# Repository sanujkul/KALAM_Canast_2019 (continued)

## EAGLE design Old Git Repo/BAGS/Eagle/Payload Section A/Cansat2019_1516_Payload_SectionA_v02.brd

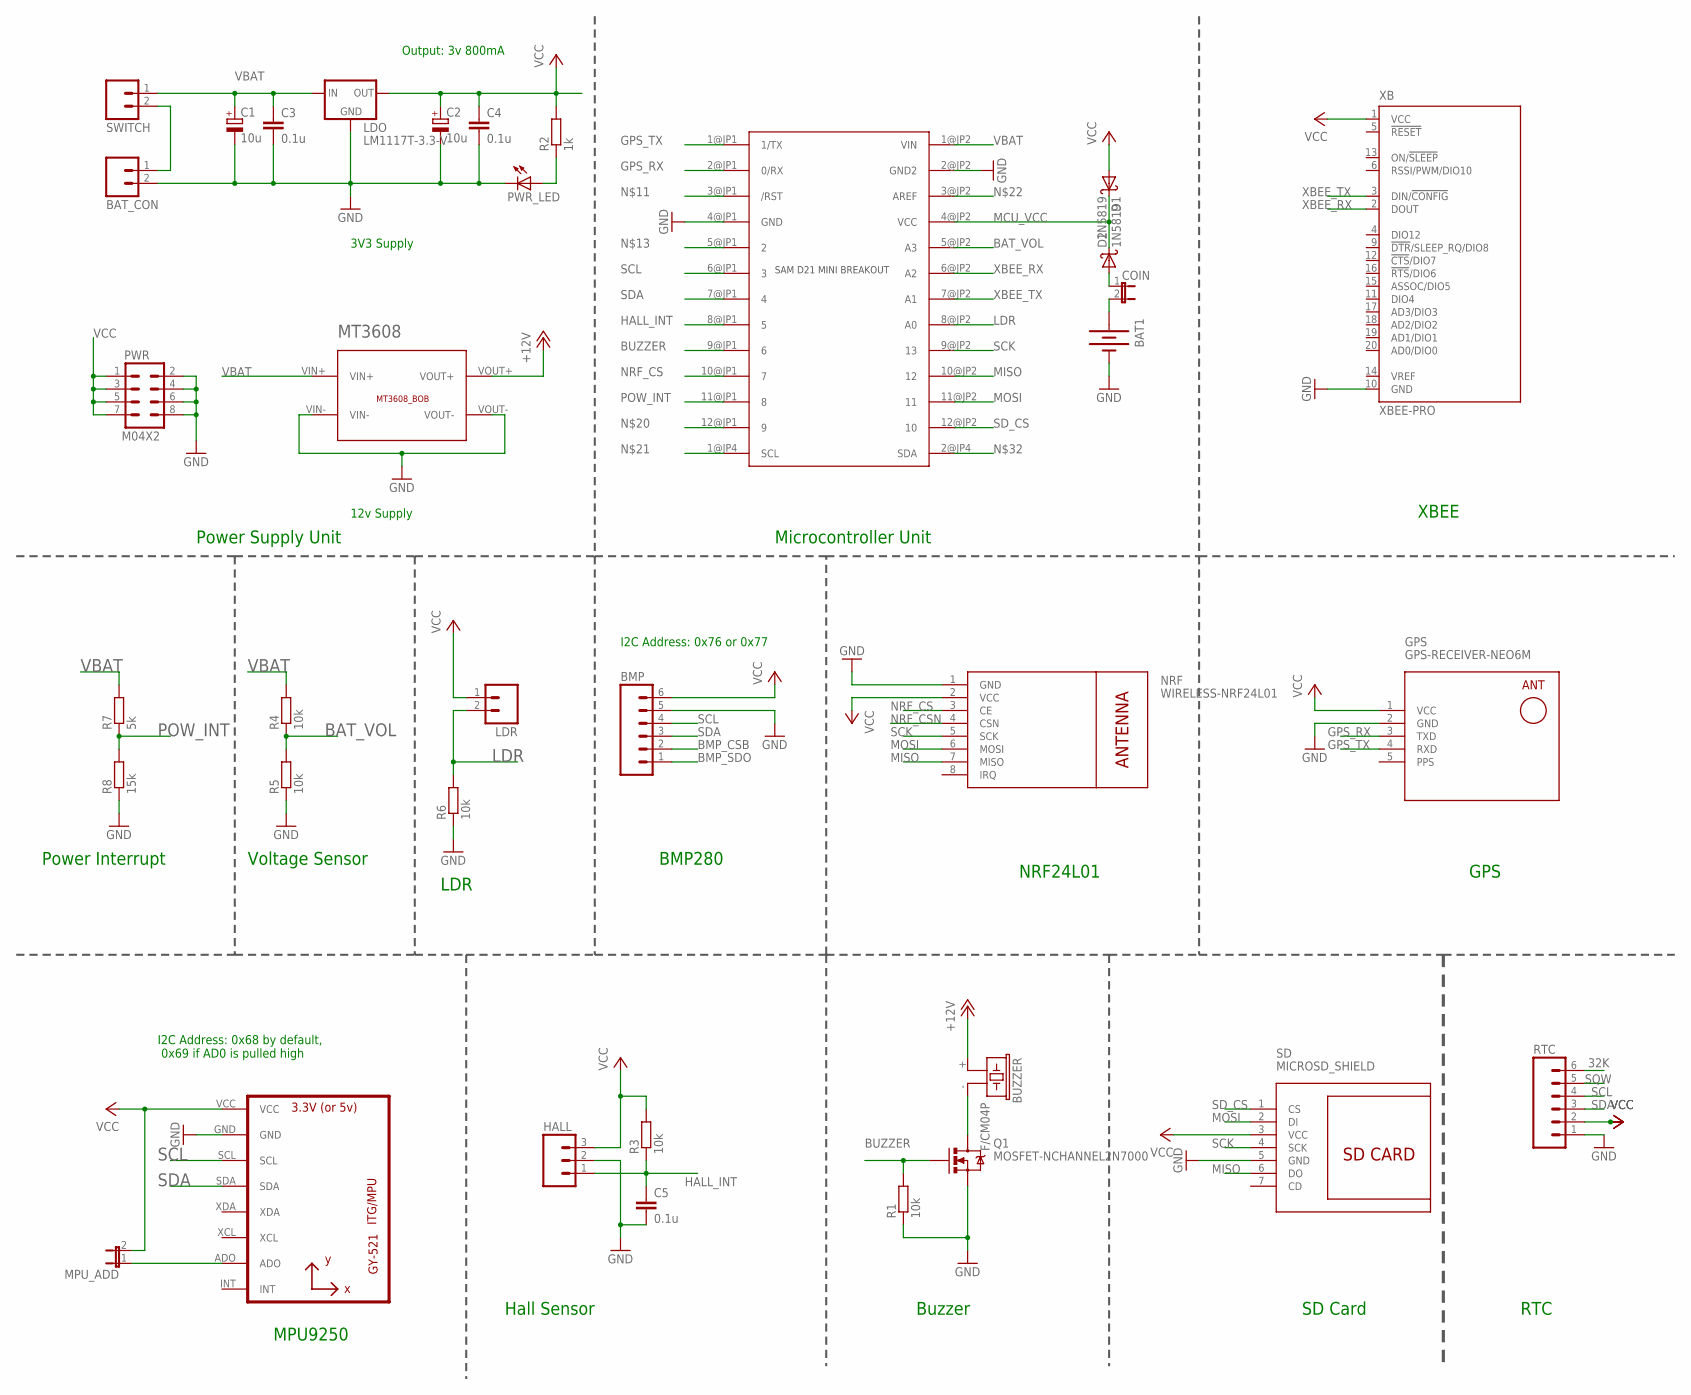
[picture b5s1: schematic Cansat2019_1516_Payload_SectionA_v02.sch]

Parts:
BAT1: BATTERY20PTH; BATTCOM_20MM_PTH
BAT_CON: M02; 02P
BMP: M06; 06P
BUZZER: F/CM04P
C1, C2: 10u; E2,5-6
C3, C4, C5: 0.1u; C025-025X050
COIN: JUMPER-2PTH; 1X02
D1, D2: 1N5819; DO41-10
GPS: GPS-RECEIVER-NEO6M
HALL: M03; 03P
LDO: LM1117T-3.3-V; TO220V
LDR: M02; 02P
MPU: GY-521MPU6050; GY-521
MPU_ADD: JUMPER-2PTH; 1X02
MT3608: MT3608_BOB
NRF: WIRELESS-NRF24L01
PWR: M04X2; 2X4
PWR_LED: LED3MM
Q1: MOSFET-NCHANNEL2N7000; TO-92
R1, R3, R4, R5, R6: 10k; 0204/7
R2: 1k; 0204/7
R7: 5k; 0204/7
R8: 15k; 0204/7
RTC: M06; 06P
SAMD: SAM_D21_MINI_BREAKOUT; JP1_SPARKFUN-SAMD21-MINI-BREAKOUT-V10
SD: MICROSD_SHIELD
SWITCH: M02; 02P
XB: XBEE-PRO

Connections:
32K: RTC.6
+12V: BUZZER.+ (1), MT3608.VOUT+
BAT_VOL: R4.1, R5.2, SAMD.5@JP2 (A3)
BMP_CSB: BMP.2
BMP_SDO: BMP.1
BUZZER: Q1.2 (G), R1.2, SAMD.9@JP1 (6)
GND: BAT1.2 (-), BAT_CON.2, BMP.5, C1.-, C2.-, C3.2, C4.2, C5.2, GPS.2 (GND), HALL.2, LDO.1 (GND), MPU.GND, MT3608.VIN-, MT3608.VOUT-, NRF.1 (GND), PWR.2, PWR.4, PWR.6, PWR.8, PWR_LED.K (C), Q1.1 (S), R1.1, R5.1, R6.1, R8.1, RTC.1, SAMD.2@JP2 (GND2), SAMD.4@JP1 (GND), SD.5 (GND), XB.10 (GND)
GPS_RX: GPS.3 (TXD), SAMD.2@JP1 (0/RX)
GPS_TX: GPS.4 (RXD), SAMD.1@JP1 (1/TX)
HALL_INT: C5.1, HALL.1, R3.1, SAMD.8@JP1 (5)
LDR: LDR.2, R6.2, SAMD.8@JP2 (A0)
MCU_VCC: D1.C, D2.C, SAMD.4@JP2 (VCC)
MISO: NRF.7 (MISO), SAMD.10@JP2 (12), SD.6 (DO)
MOSI: NRF.6 (MOSI), SAMD.11@JP2 (11), SD.2 (DI)
unnamed: BUZZER.- (2), Q1.3 (D)
unnamed: COIN.1, D2.A
unnamed: PWR_LED.A, R2.1
unnamed: BAT1.1 (+), COIN.2
unnamed: BAT_CON.1, SWITCH.2
unnamed: MPU.ADO, MPU_ADD.1
NRF_CS: NRF.3 (CE), SAMD.10@JP1 (7)
NRF_CSN: NRF.4 (CSN)
POW_INT: R7.1, R8.2, SAMD.11@JP1 (8)
PPS: GPS.5 (PPS)
SCK: NRF.5 (SCK), SAMD.9@JP2 (13), SD.4 (SCK)
SCL: BMP.4, MPU.SCL, RTC.4, SAMD.6@JP1 (3)
SDA: BMP.3, MPU.SDA, RTC.3, SAMD.7@JP1 (4)
SD_CS: SAMD.12@JP2 (10), SD.1 (CS)
SQW: RTC.5
VBAT: C1.+, C3.1, LDO.3 (IN), MT3608.VIN+, R4.2, R7.2, SAMD.1@JP2 (VIN), SWITCH.1
VCC: BMP.6, C2.+, C4.1, D1.A, GPS.1 (VCC), HALL.3, LDO.2 (OUT), LDR.1, MPU.VCC, MPU_ADD.2, NRF.2 (VCC), PWR.1, PWR.3, PWR.5, PWR.7, R2.2, R3.2, RTC.2, SD.3 (VCC), XB.1 (VCC)
XBEE_RX: SAMD.6@JP2 (A2), XB.2 (DOUT)
XBEE_TX: SAMD.7@JP2 (A1), XB.3 (DIN/!CONFIG)

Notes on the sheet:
Power Supply Unit
3V3 Supply
12v Supply
Output: 3v 800mA
Microcontroller Unit
Buzzer
Voltage Sensor
BMP280
GPS
XBEE
MPU9250
SD Card
NRF24L01
LDR
Hall Sensor
I2C Address: 0x76 or 0x77
I2C Address: 0x68 by default, 0x69 if AD0 is pulled high
RTC
Power Interrupt

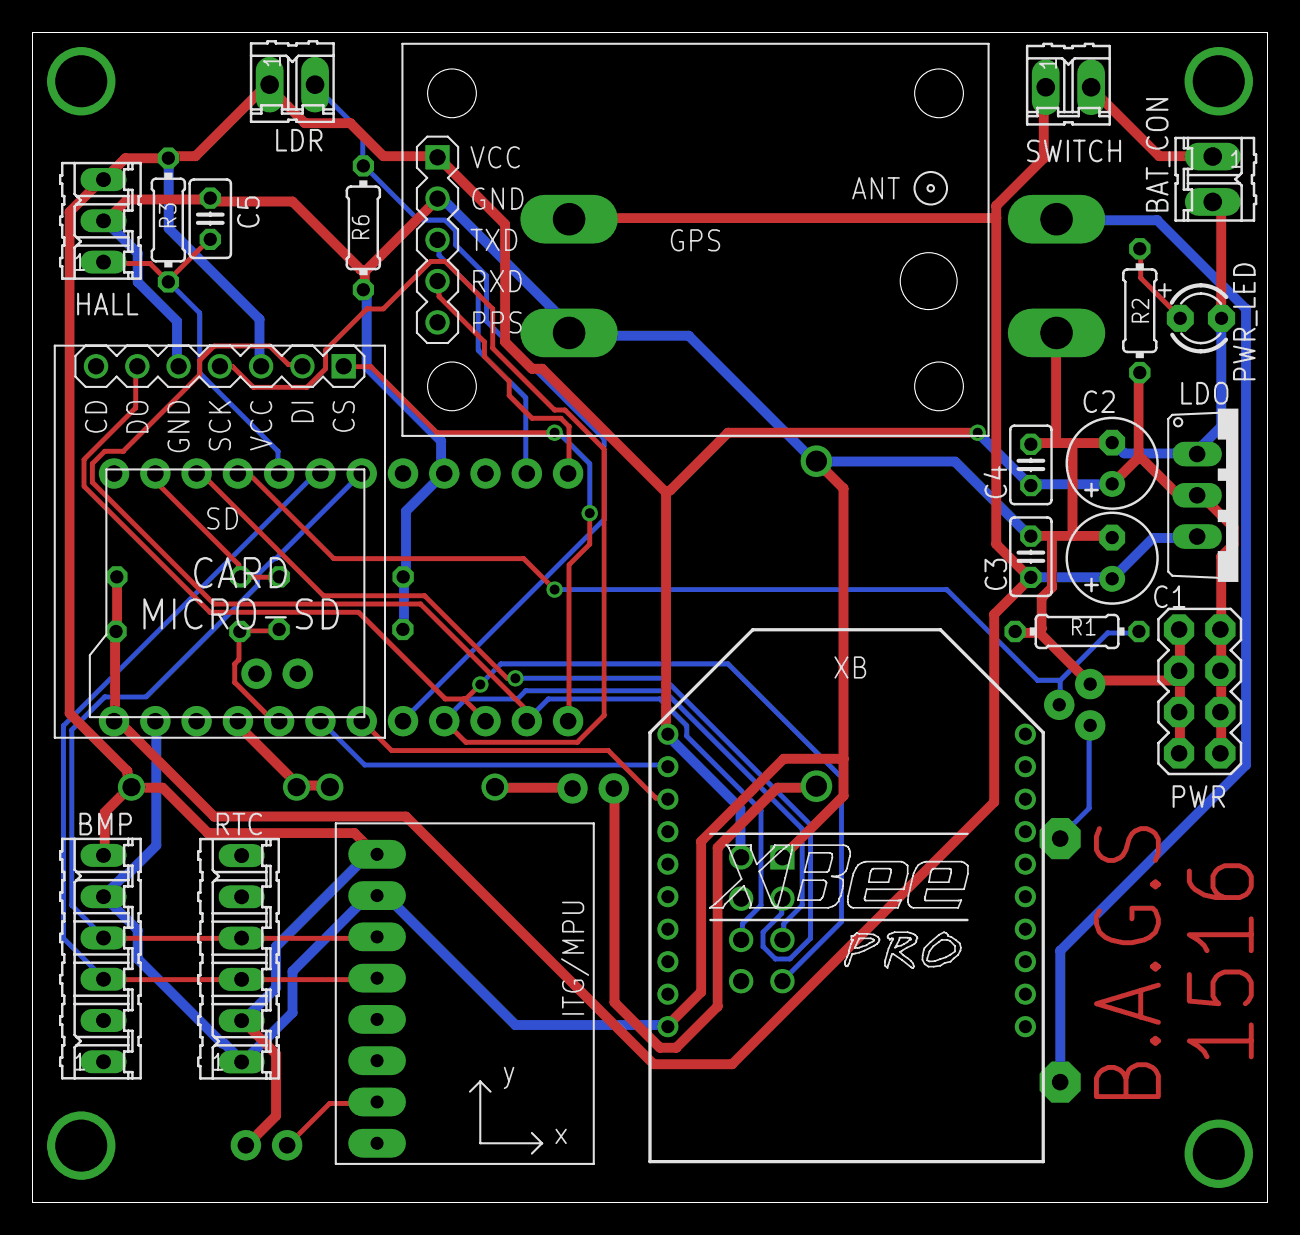
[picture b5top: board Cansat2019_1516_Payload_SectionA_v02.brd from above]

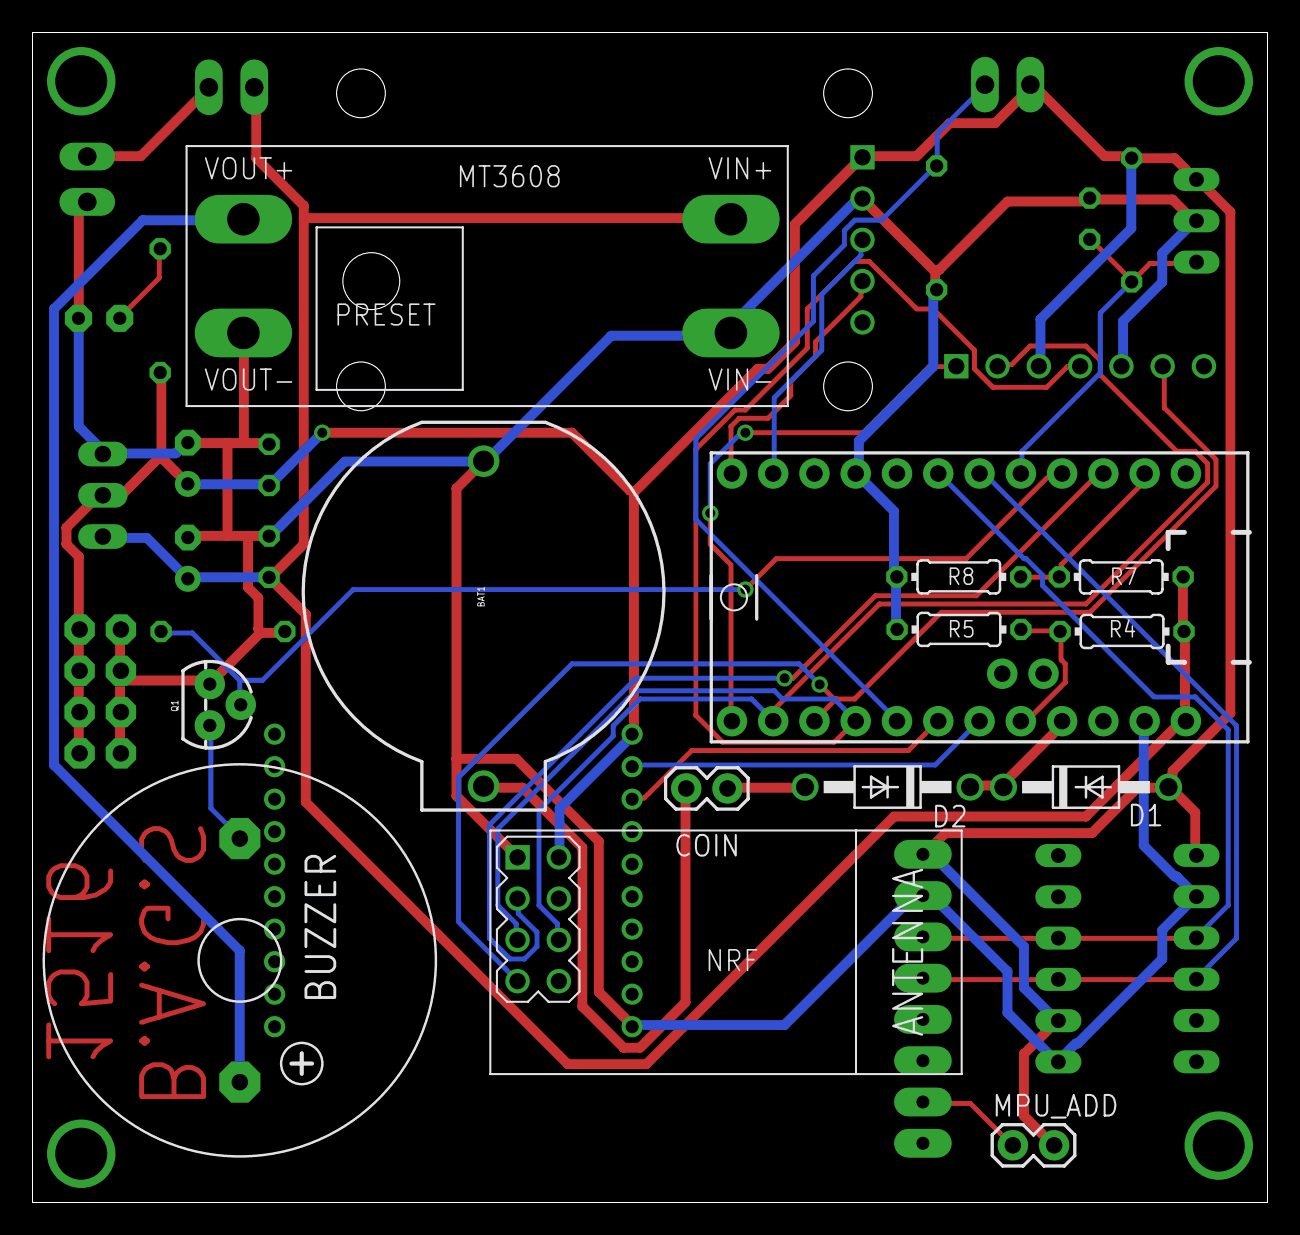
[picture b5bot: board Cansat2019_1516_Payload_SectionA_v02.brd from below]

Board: 2 copper layers, 76.0 x 72.0 mm, 36 parts (14 on the bottom side), 27 nets.

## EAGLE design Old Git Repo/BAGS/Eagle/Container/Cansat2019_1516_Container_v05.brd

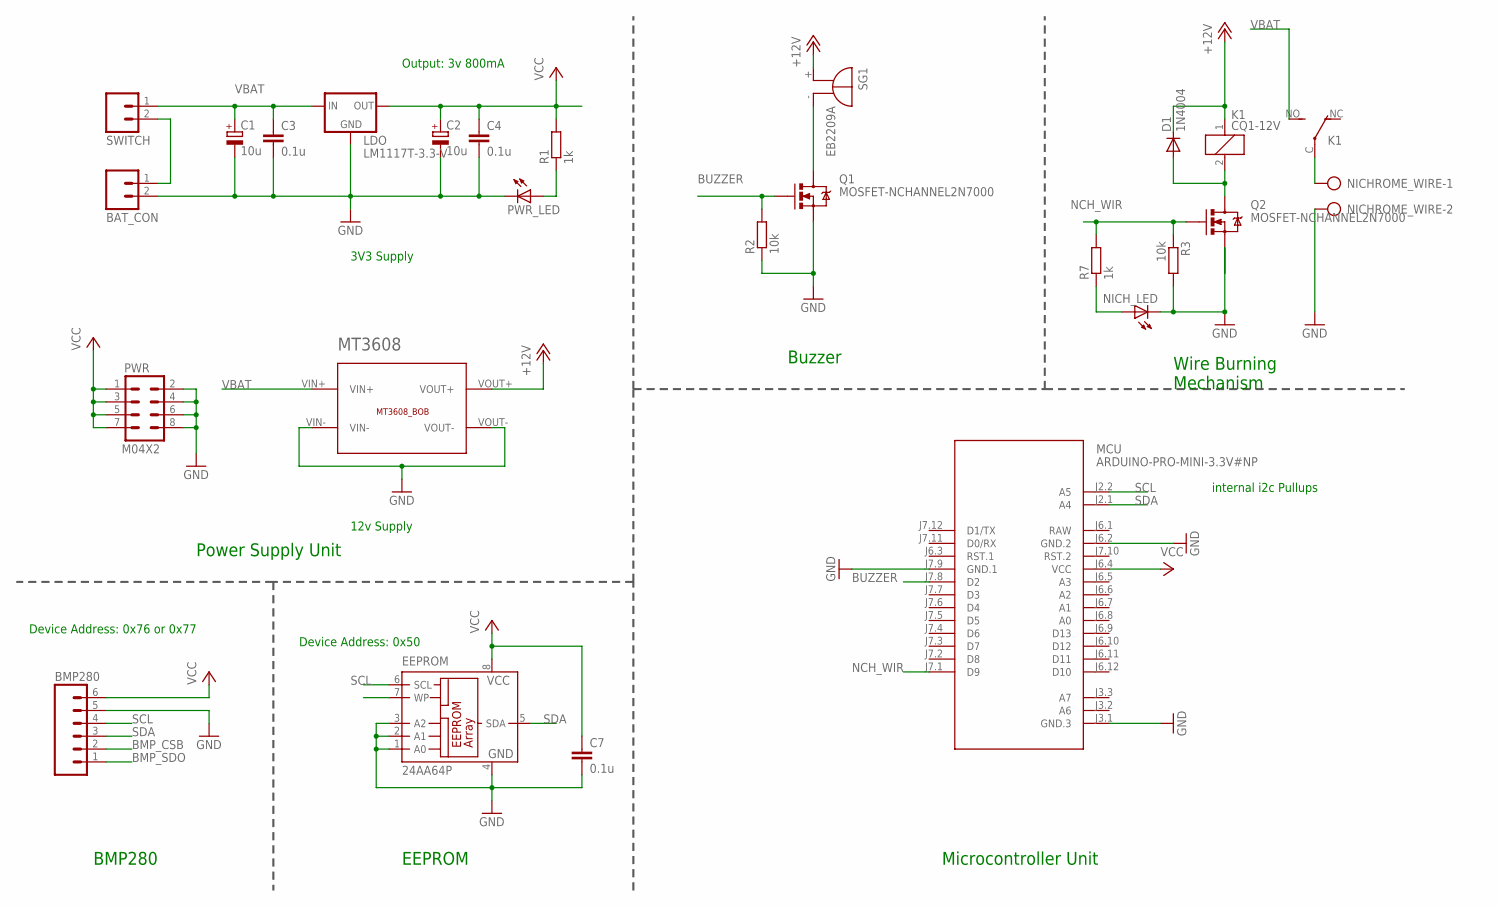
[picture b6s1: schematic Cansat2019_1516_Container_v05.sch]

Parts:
BAT_CON: M02; 02P
BMP280: M06; 06P
C1, C2: 10u; E2,5-6
C3, C4, C7: 0.1u; C025-025X050
D1: 1N4004; DO41-10
EEPROM: 24AA64P; DIL8
K1: CQ1-12V; CQ1
LDO: LM1117T-3.3-V; TO220V
MCU: ARDUINO-PRO-MINI-3.3V#NP; ARDUINO-PRO-MINI#NP
MT3608: MT3608_BOB
NICHROME_WIRE: AK500/2-H
NICH_LED: LED3MM
PWR: M04X2; 2X4
PWR_LED: LED3MM
Q1, Q2: MOSFET-NCHANNEL2N7000; TO-92
R1, R7: 1k; 0204/7
R2, R3: 10k; 0204/7
SG1: EB2209A
SWITCH: M02; 02P

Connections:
+12V: D1.C, K1.1, MT3608.VOUT+, SG1.+
BMP_CSB: BMP280.2
BMP_SDO: BMP280.1
BUZZER: MCU.J7.8 (D2), Q1.2 (G), R2.2
GND: BAT_CON.2, BMP280.5, C1.-, C2.-, C3.2, C4.2, C7.2, EEPROM.1 (A0), EEPROM.2 (A1), EEPROM.3 (A2), EEPROM.4 (GND), LDO.1 (GND), MCU.J3.1 (GND.3), MCU.J6.2 (GND.2), MCU.J7.9 (GND.1), MT3608.VIN-, MT3608.VOUT-, NICHROME_WIRE.2, NICH_LED.K (C), PWR.2, PWR.4, PWR.6, PWR.8, PWR_LED.K (C), Q1.1 (S), Q2.1 (S), R2.1, R3.2
unnamed: Q1.3 (D), SG1.-
unnamed: K1.C, NICHROME_WIRE.1
unnamed: PWR_LED.A, R1.1
unnamed: NICH_LED.A, R7.1
unnamed: BAT_CON.1, SWITCH.2
unnamed: D1.A, K1.2, Q2.3 (D)
NCH_WIR: MCU.J7.1 (D9), Q2.2 (G), R3.1, R7.2
RAW: MCU.J6.1 (RAW)
SCL: BMP280.4, EEPROM.6 (SCL), MCU.J2.2 (A5)
SDA: BMP280.3, EEPROM.5 (SDA), MCU.J2.1 (A4)
VBAT: C1.+, C3.1, K1.NO (S), LDO.3 (IN), MT3608.VIN+, SWITCH.1
VCC: BMP280.6, C2.+, C4.1, C7.1, EEPROM.8 (VCC), LDO.2 (OUT), MCU.J6.4 (VCC), PWR.1, PWR.3, PWR.5, PWR.7, R1.2

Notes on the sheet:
Power Supply Unit
Buzzer
Wire Burning Mechanism
Microcontroller Unit
3V3 Supply
12v Supply
BMP280
internal i2c Pullups
Output: 3v 800mA
Device Address: 0x50
EEPROM
Device Address: 0x76 or 0x77

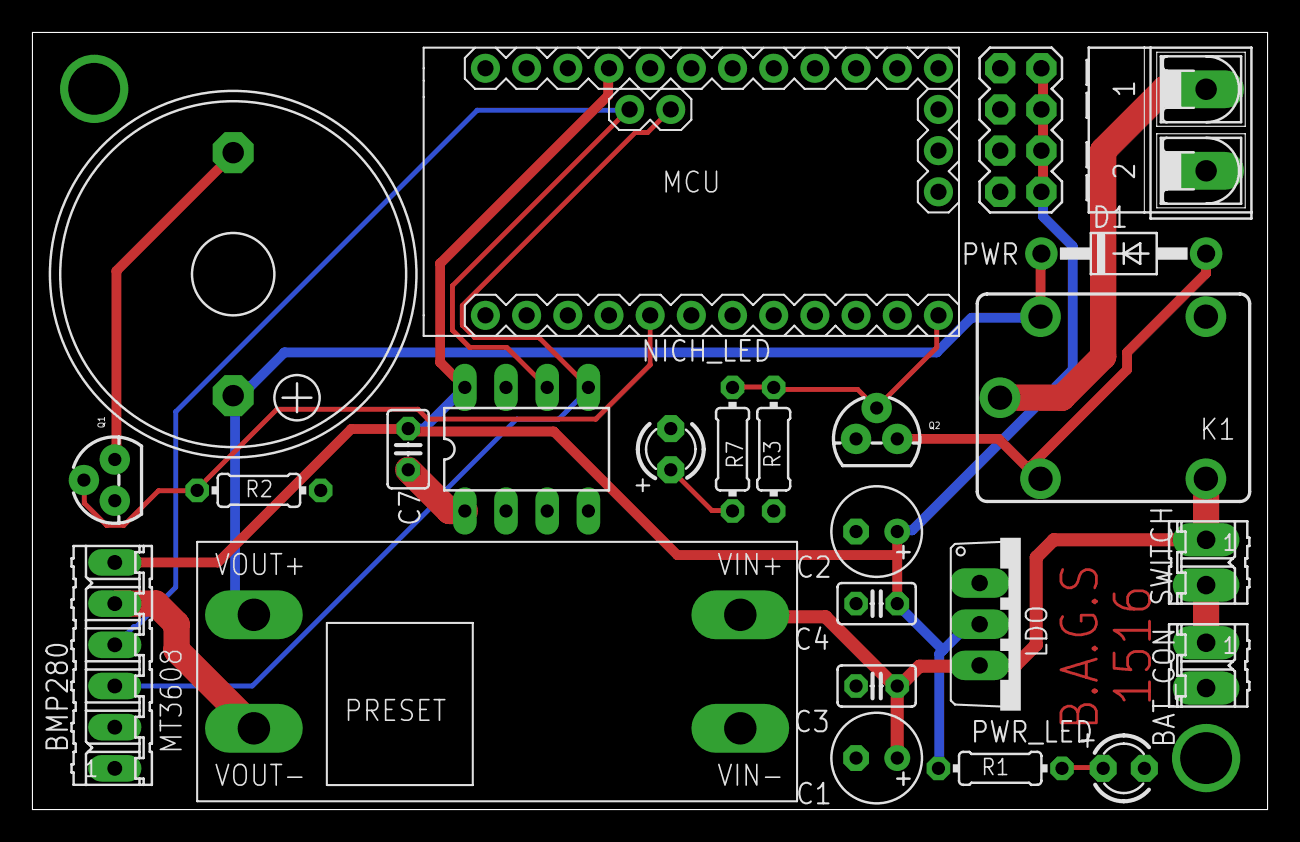
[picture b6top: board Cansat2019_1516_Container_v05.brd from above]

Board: 2 copper layers, 76.2 x 47.9 mm, 25 parts (0 on the bottom side), 14 nets.

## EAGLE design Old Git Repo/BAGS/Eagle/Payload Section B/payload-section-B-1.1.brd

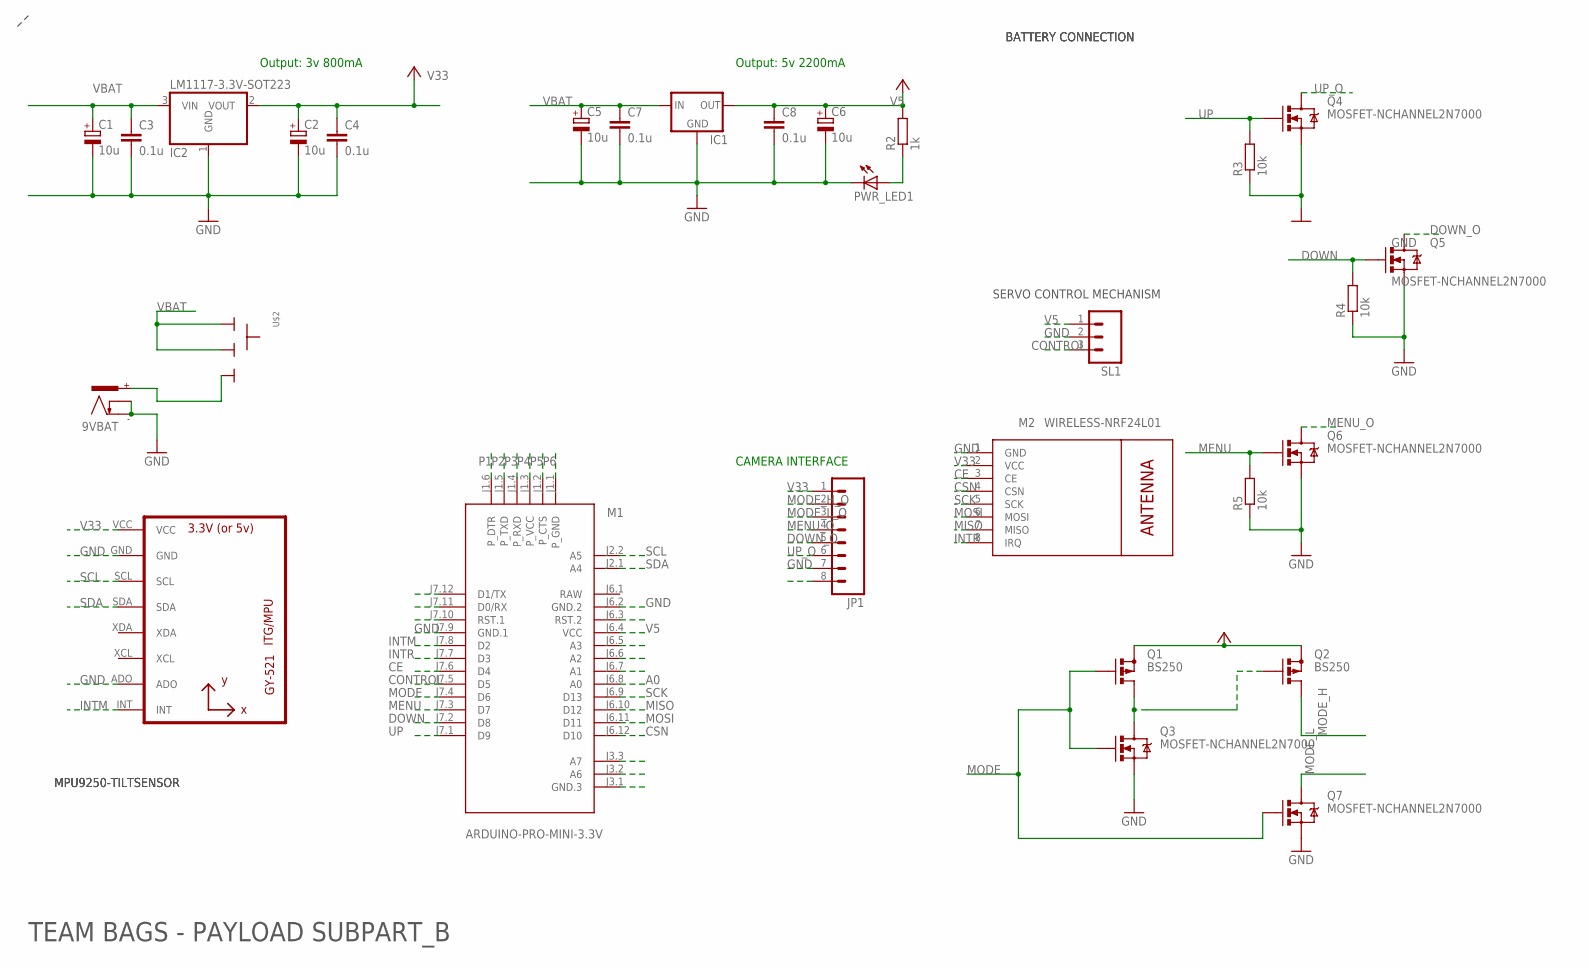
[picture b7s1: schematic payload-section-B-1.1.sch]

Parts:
9VBAT: POWER_CON; NEB21R
C1, C2, C5, C6: 10u; CT6032
C3, C4, C7, C8: 0.1u; C0805
IC1: V_REG_78XX-TO-220; TO-220-ALT
IC2: LM1117-3.3V-SOT223; SOT223
JP1: M08; 08P
M1: ARDUINO-PRO-MINI-3.3V; ARDUINO-PRO-MINI
M2: WIRELESS-NRF24L01
PWR_LED1: LED3MM
Q1, Q2: BS250; SOT54E
Q3, Q4, Q5, Q6, Q7: MOSFET-NCHANNEL2N7000; TO-92
R2: 1k; R0805
R3, R4, R5: 10k; R0805
SL1: M03; 03P
U2: GY-521MPU6050; GY-521
U$2: SLIDESWITCH-BIG; BIGSWITCH

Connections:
A0: M1.J6.8 (A0)
CE: M1.J7.6 (D4), M2.3 (CE)
CONTROL: M1.J7.5 (D5), SL1.3
CSN: M1.J6.12 (D10), M2.4 (CSN)
DOWN: M1.J7.2 (D8), Q5.2 (G), R4.2
DOWN_O: JP1.5, Q5.3 (D)
GND: 9VBAT.-, 9VBAT.C, C1.-, C2.-, C3.2, C4.2, C5.-, C6.-, C7.2, C8.2, IC1.GND, IC2.1 (GND), JP1.7, M1.J6.2 (GND.2), M1.J7.9 (GND.1), M2.1 (GND), PWR_LED1.K (C), Q3.1 (S), Q4.1 (S), Q5.1 (S), Q6.1 (S), Q7.1 (S), R3.1, R4.1, R5.1, SL1.2, U2.ADO, U2.GND
INTM: M1.J7.8 (D2), U2.INT
INTR: M1.J7.7 (D3), M2.8 (IRQ)
MENU: M1.J7.3 (D7), Q6.2 (G), R5.2
MENU_O: JP1.4, Q6.3 (D)
MISO: M1.J6.10 (D12), M2.7 (MISO)
MODE: M1.J7.4 (D6), Q1.G, Q3.2 (G), Q7.2 (G)
MODE_H: Q2.D
MODE_H_O: JP1.2
MODE_L: Q7.3 (D)
MODE_L_O: JP1.3
MOSI: M1.J6.11 (D11), M2.6 (MOSI)
unnamed: 9VBAT.+, U$2.3
unnamed: Q1.D, Q2.G, Q3.3 (D)
unnamed: PWR_LED1.A, R2.1
P1: M1.J1.6 (P_DTR)
P2: M1.J1.5 (P_TXD)
P3: M1.J1.4 (P_RXD)
P4: M1.J1.3 (P_VCC)
P5: M1.J1.2 (P_CTS)
P6: M1.J1.1 (P_GND)
RAW: M1.J6.1 (RAW)
SCK: M1.J6.9 (D13), M2.5 (SCK)
SCL: M1.J2.2 (A5), U2.SCL
SDA: M1.J2.1 (A4), U2.SDA
UP: M1.J7.1 (D9), Q4.2 (G), R3.2
UP_O: JP1.6, Q4.3 (D)
V5: C6.+, C8.1, IC1.OUT, M1.J6.4 (VCC), R2.2, SL1.1
V33: C2.+, C4.1, IC2.2 (VOUT), JP1.1, M2.2 (VCC), U2.VCC
VBAT: C1.+, C3.1, C5.+, C7.1, IC1.IN, IC2.3 (VIN), U$2.1, U$2.2
VCC: Q1.S, Q2.S

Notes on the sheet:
Output: 3v 800mA
Output: 5v 2200mA
MPU9250-TILTSENSOR
BATTERY CONNECTION
SERVO CONTROL MECHANISM
CAMERA INTERFACE
TEAM BAGS - PAYLOAD SUBPART_B

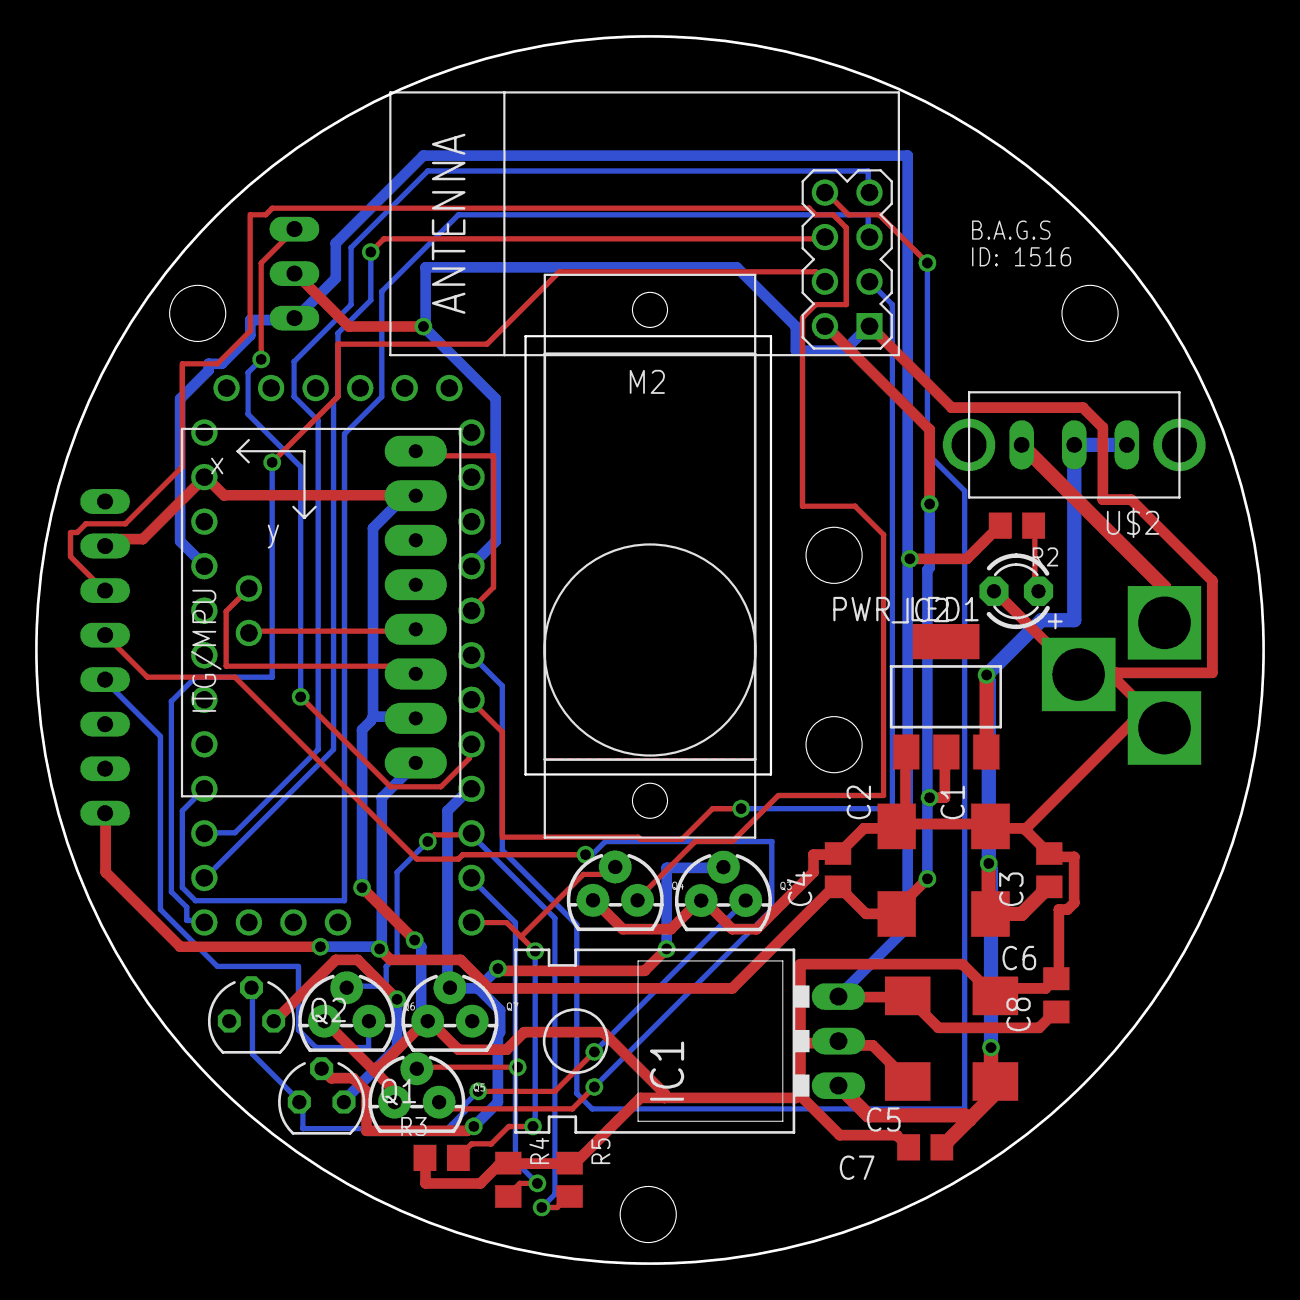
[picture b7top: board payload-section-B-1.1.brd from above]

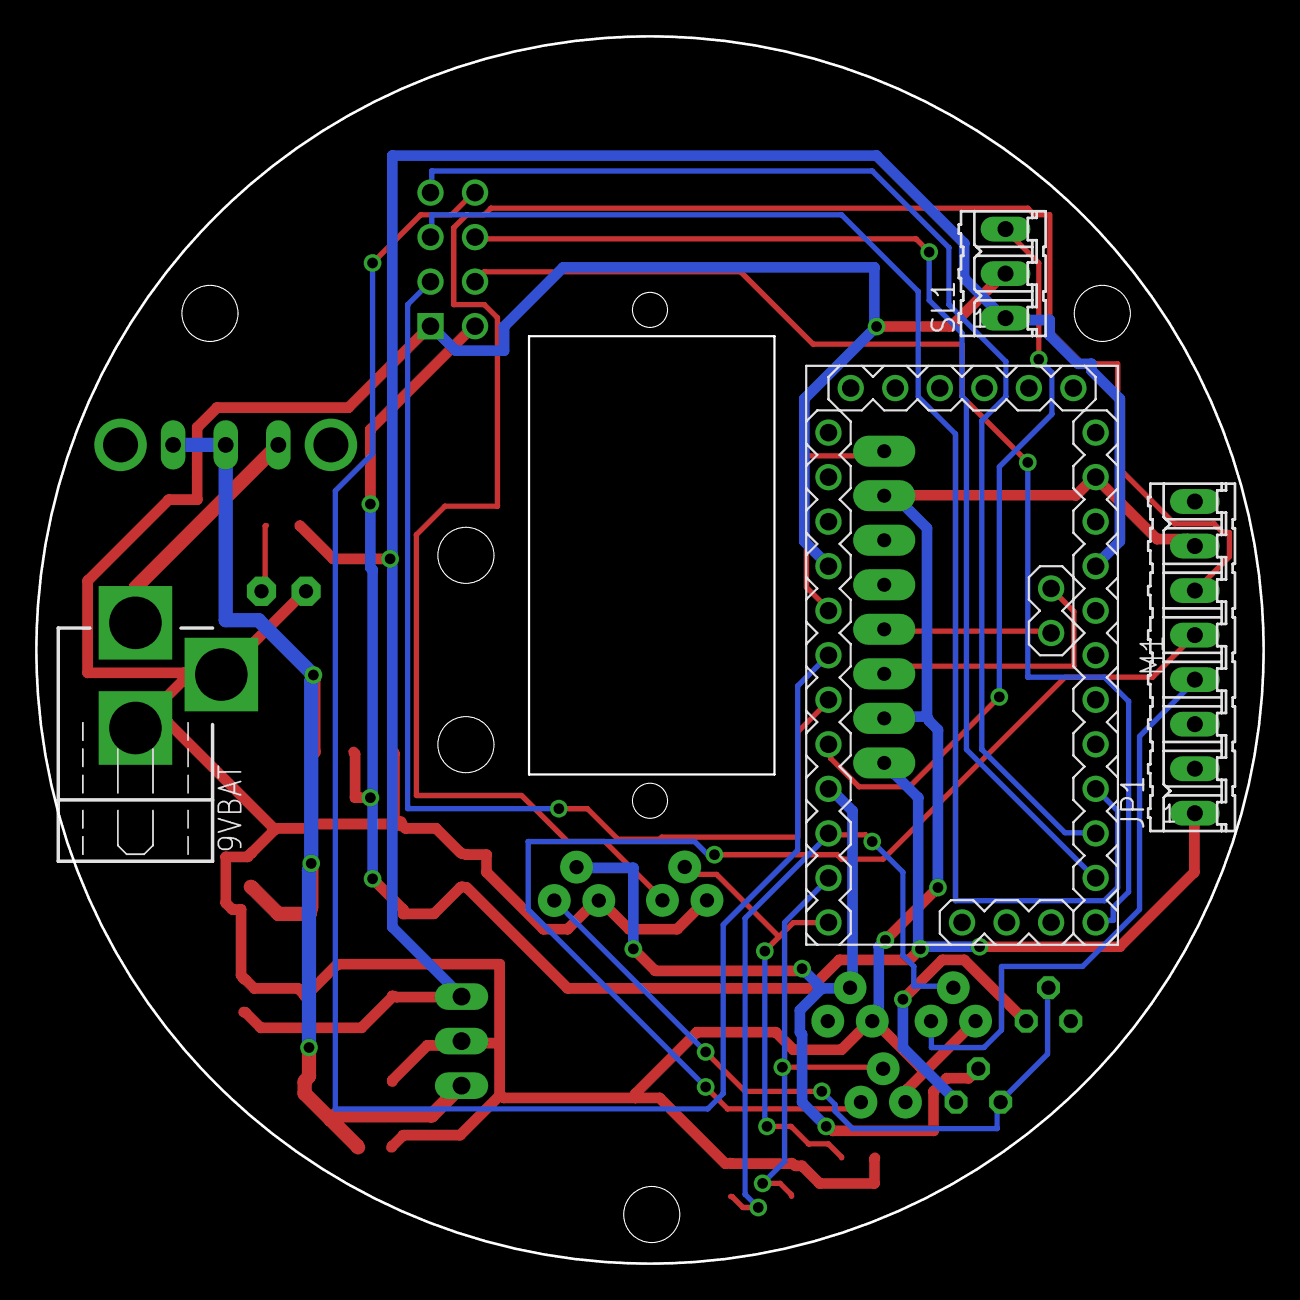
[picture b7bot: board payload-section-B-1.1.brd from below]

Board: 2 copper layers, 70.0 x 70.0 mm, 30 parts (4 on the bottom side), 25 nets.

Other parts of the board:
U$1: SG90_TOP

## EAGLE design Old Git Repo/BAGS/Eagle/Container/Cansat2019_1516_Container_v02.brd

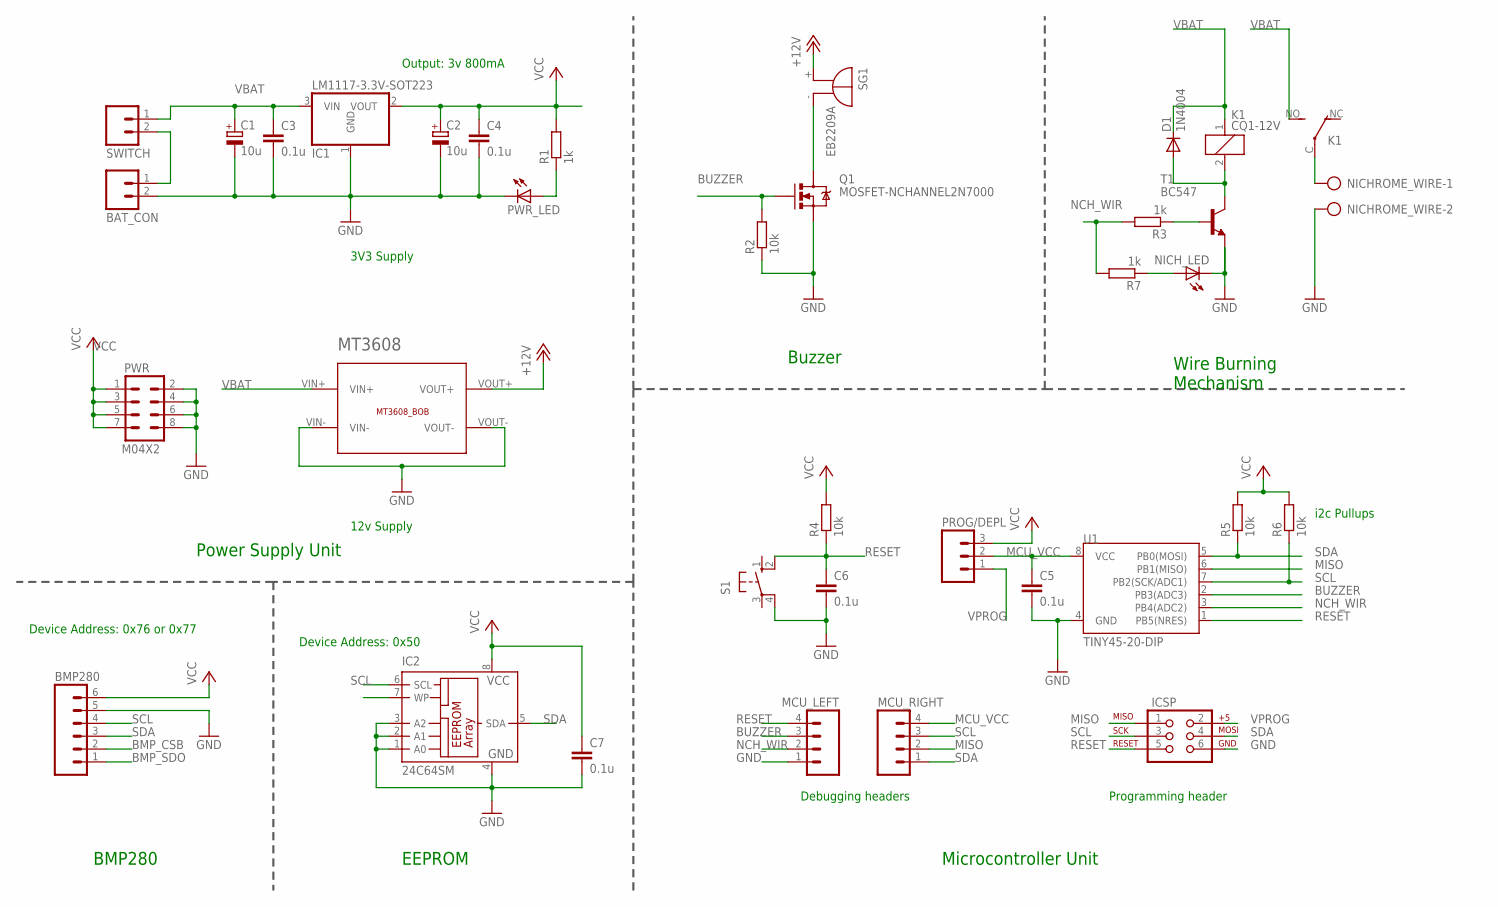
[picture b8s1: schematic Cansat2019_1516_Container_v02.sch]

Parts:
BAT_CON: M02; 02P
BMP280: M06; 06P
C1, C2: 10u; E2,5-6
C3, C4, C5, C6, C7: 0.1u; C025-025X050
D1: 1N4004; DO41-10
IC1: LM1117-3.3V-SOT223; SOT223
IC2: 24C64SM; SO-08M
ICSP: AVR_SPI_PRG_6NS; 2X3-NS
K1: CQ1-12V; CQ1
MCU_LEFT: M04; 04P
MCU_RIGHT: M04; 04P
MT3608: MT3608_BOB
NICHROME_WIRE: AK500/2-H
NICH_LED: LED3MM
PROG/DEPL: M03PTH; 1X03
PWR: M04X2; 2X4
PWR_LED: LED3MM
Q1: MOSFET-NCHANNEL2N7000; TO-92
R1, R3, R7: 1k; 0204/7
R2, R4, R5, R6: 10k; 0204/7
S1: PUSH-BUTTON-6MM; B3F-10XX
SG1: EB2209A
SWITCH: M02; 02P
T1: BC547; TO92
U1: TINY45-20-DIP; DIP08

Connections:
+12V: MT3608.VOUT+, SG1.+
BMP_CSB: BMP280.2
BMP_SDO: BMP280.1
BUZZER: MCU_LEFT.3, Q1.2 (G), R2.2, U1.2 (PB3(ADC3))
GND: BAT_CON.2, BMP280.5, C1.-, C2.-, C3.2, C4.2, C5.2, C6.2, C7.2, IC1.1 (GND), IC2.1 (A0), IC2.2 (A1), IC2.3 (A2), IC2.4 (GND), ICSP.6, MCU_LEFT.1, MT3608.VIN-, MT3608.VOUT-, NICHROME_WIRE.2, NICH_LED.K (C), PWR.2, PWR.4, PWR.6, PWR.8, PWR_LED.K (C), Q1.1 (S), R2.1, S1.4 (P1), U1.4 (GND)
MCU_VCC: C5.1, MCU_RIGHT.4, PROG/DEPL.2, U1.8 (VCC)
MISO: ICSP.1, MCU_RIGHT.2, U1.6 (PB1(MISO))
unnamed: Q1.3 (D), SG1.-
unnamed: K1.C, NICHROME_WIRE.1
unnamed: PWR_LED.A, R1.1
unnamed: R3.1, T1.2 (B)
unnamed: NICH_LED.A, R7.1
unnamed: BAT_CON.1, SWITCH.2
unnamed: D1.A, K1.2, T1.3 (C)
NCH_WIR: MCU_LEFT.2, R3.2, R7.2, U1.3 (PB4(ADC2))
RESET: C6.1, ICSP.5, MCU_LEFT.4, R4.1, S1.2 (S1), U1.1 (PB5(NRES))
SCL: BMP280.4, IC2.6 (SCL), ICSP.3, MCU_RIGHT.3, R6.1, U1.7 (PB2(SCK/ADC1))
SDA: BMP280.3, IC2.5 (SDA), ICSP.4, MCU_RIGHT.1, R5.1, U1.5 (PB0(MOSI))
VBAT: C1.+, C3.1, D1.C, IC1.3 (VIN), K1.1, K1.NO (S), MT3608.VIN+, SWITCH.1
VCC: BMP280.6, C2.+, C4.1, C7.1, IC1.2 (VOUT), IC2.8 (VCC), PROG/DEPL.3, PWR.1, PWR.3, PWR.5, PWR.7, R1.2, R4.2, R5.2, R6.2
VPROG: ICSP.2, PROG/DEPL.1

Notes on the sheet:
Power Supply Unit
Buzzer
Wire Burning Mechanism
Debugging headers
Programming header
Microcontroller Unit
3V3 Supply
12v Supply
BMP280
i2c Pullups
Output: 3v 800mA
Device Address: 0x50
EEPROM
Device Address: 0x76 or 0x77

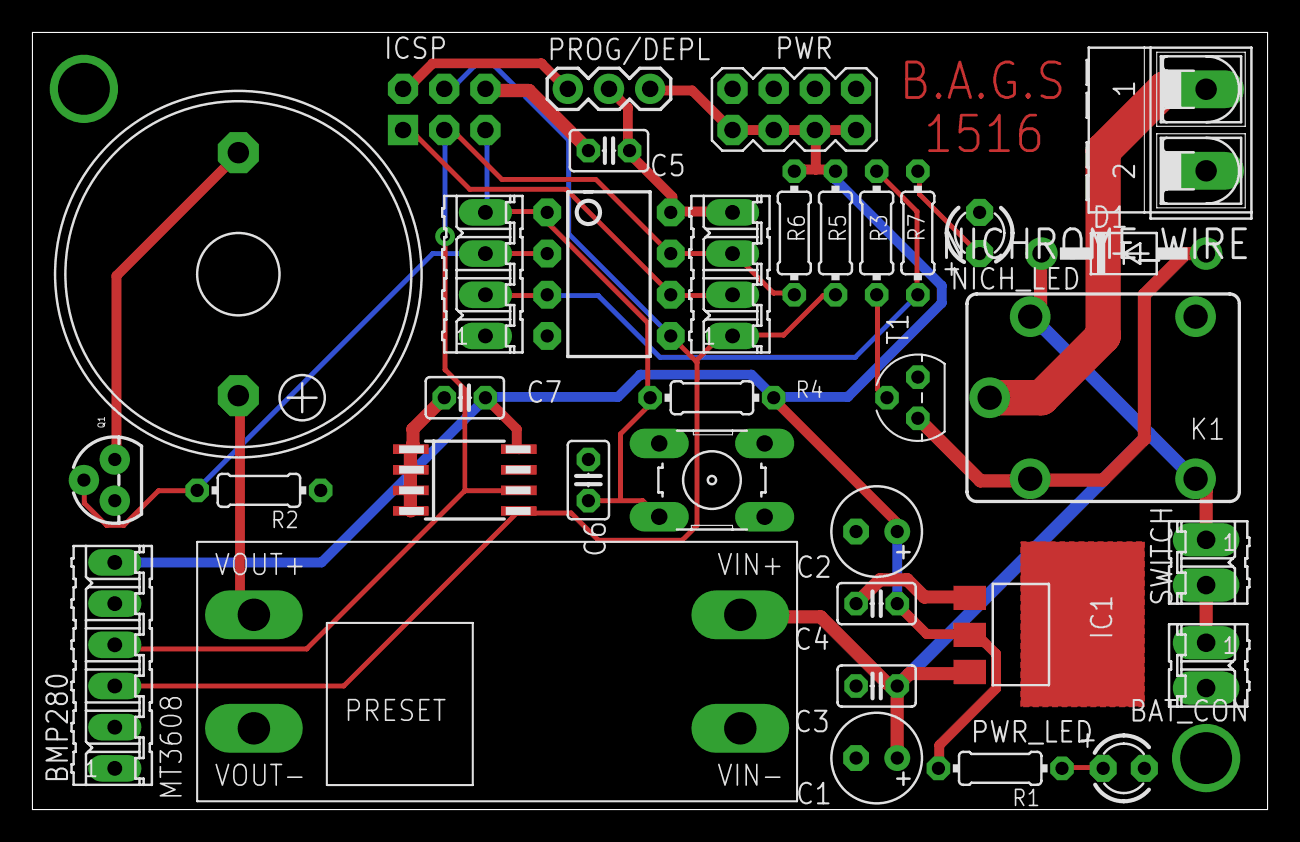
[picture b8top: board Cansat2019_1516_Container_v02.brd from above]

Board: 2 copper layers, 76.2 x 47.9 mm, 35 parts (0 on the bottom side), 19 nets.

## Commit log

2019-05-11 One more commit
2019-05-11 GPS_FIX_Test_1_Successful
2019-05-11 GPS FIXED, But MPU disturbed
2019-05-11 Fixed MPU with GPS
2019-05-12 MPU only works when code is uploaded, else doesnt
2019-05-12 Fixed by updating MPU in smart Delay :) ;)
2019-05-12 XBEE Calibration command added with Fixed GPS and MPU, BOOM BOOM :) ;)
2019-05-17 ADDED BMP and MPU callibration interrupt command
2019-05-17 CameraStabilization Beins
2019-05-17 Minor change to keep MPU output between -180 to 180
2019-05-18 Trying to use PID with camera stabilization code
2019-05-24 Bluetooth_Test
    Bluetooth_Test_24/05/19
2019-05-24 Some minor changes
2019-05-24 Bluetooth Master code for Teensy
2019-05-24 Better version of 3
2019-05-24 complete PCB Tested code with Bluetooth too
2019-05-24 some moinor changes
2019-05-25 Added Camera Code
2019-05-27 Making camera software
2019-05-27 Minor changes to camera functioning code
2019-05-27 Thinking of better logic for Camera On, avoiding delay
2019-05-27 Added Bluetooth Logic ;)
2019-05-27 Stabilize + Bluetooth + Camera ;) ;)
2019-05-28 SD CARD CODE FOR POWER CUTOFF
2019-05-29 Feature for Power loss added
2019-05-29 updated Software State
2019-05-29 Added more #define SER_DEBUG
2019-06-03 Improving logic
2019-06-03 No cahnge: Organised in folders
2019-06-14 4 : Complete code with removed SD bugs, 4b:Adding hacks
2019-06-15 added mpu logic
2019-06-20 Cansat Competition Finished
2019-06-20 All other documents added
2019-06-20 add packets csv from sd and telemetry
2020-02-24 creating Readme
